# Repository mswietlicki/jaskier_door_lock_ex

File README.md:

# 12 V Linear-Actuator Door Lock

ESPHome door lock for Home Assistant: an ESP32 drives a **DRV8871** H-bridge into a
12 V linear actuator, with an **INA219** high-side shunt reading motor current.
End of travel *and* obstructions are both detected from that current — no extra sensors.
Powered from a 4S LiFePO₄ pack via an **MH-MINI-360** buck.

Three variants share the same per-door state machine:

| Variant | Config | ESP | Doors |
|---|---|---|---|
| **A** | `door_lock_a.yaml` | ESP32-C3-Zero (Waveshare) | 1 |
| **B** | `door_lock_b.yaml` | ESP32-S3-DevKitC-1 | 4, fully independent, one board |
| **C** | `door_lock_c.yaml` + [`hardware/door-lock-c/`](hardware/door-lock-c/README.md) | ESP32-C3 SuperMini, socketed | 2, on a hand-assembled JLCPCB board with door contacts and optional RS485 (Modbus RTU) |

Everything below describes variant A; [Variant B](#variant-b--four-doors-one-board)
documents only what differs (pins, addresses, BOM, power). Variant C is documented with its
board in [`hardware/door-lock-c/README.md`](hardware/door-lock-c/README.md).

| | |
|---|---|
| Pack | 4S LiFePO₄ · 12.8 V nominal · 10.0 – 14.6 V |
| Measured stall current | ≈ 0.50 A |
| Default thresholds | 0.40 A stall / 0.60 A hard limit / 0.01 A idle |
| Shunt | 0.1 Ω · 0.8 mA resolution |
| I²C | GPIO8 (SDA) / GPIO9 (SCL) · address 0x40 |
| Bridge | GPIO6 (IN1) / GPIO7 (IN2) · full on/off, **no PWM** |

## Repository layout

```
hardware/door-lock-c/        variant C - two-door PCB (KiCad 10, JLCPCB files, generator scripts)
door_lock_a.yaml             variant A - single door on an ESP32-C3-Zero
door_lock_b.yaml             variant B - four doors on an ESP32-S3-DevKitC-1
door_lock_c.yaml             variant C - two doors, door contacts, Modbus RTU on RS485
packages/door.yaml           one door's state machine (variants B and C)
packages/door_switches.yaml  one door's position switches + button (variant B)
packages/door_contact.yaml   one door's wired magnetic contact (variant C)
secrets.yaml.example         copy to secrets.yaml and fill in
docs/wiring.html             full illustrated build document for variant A
docs/wiring_b.html           full illustrated build document for variant B
docs/diagrams/
  fig1-wiring.svg            complete wiring diagram, all pinouts (variant A)
  fig2-position-switches.svg optional position feedback
  fig3-move-outcomes.svg     how a move terminates
  figB1-wiring.svg           complete wiring diagram, four doors (variant B)
```

---

## Read this first

> [!CAUTION]
> **Set the buck converter output before connecting anything to it.**
> The MH-MINI-360 ships with its trimpot in an arbitrary position and will happily pass
> close to 12 V straight through. The ESP32-C3-Zero's `5V` pad accepts **3.7 – 6 V**;
> above that you destroy the regulator and probably the chip.
> Wire U4 to the pack *with nothing on its output*, measure OUT+ to OUT−, trim to
> **5.00 V**, power down, then connect U1.

> [!WARNING]
> **Two things a door lock has to get right.** Keep a mechanical override — a key
> cylinder or thumb turn — that works with the electronics dead. And make sure the
> actuator cannot trap anyone inside: the bolt must be releasable from the protected
> side without power.

The firmware drives the bridge **fully on, never PWM**. PWM would chop the current the
INA219 sees and make stall detection unreliable, so the actuator only ever runs at full
speed. Adding soft-start later means an RC filter on the sense path and higher thresholds.

---

## Wiring

**The current path is the whole design.** Pack → F1 → +12 V rail → U3's 0.1 Ω shunt →
U2 Power + → motor. Because the shunt sits upstream of the bridge, one INA219 gives you
both motor current *and* pack voltage, and its bus-voltage input never sees the chopped
motor node. U3's own GND runs back to the star point as a separate wire so motor return
current does not corrupt the measurement.

U2's `VM` and `GND` header pins are the same nets as the `Power ±` screw terminal —
populate one or the other, not both.

### Net list

Build in this order. Everything in the 12 V group carries motor current: keep it short,
thick, and away from the I²C pair.

| Net | From | To | Wire | Notes |
|---|---|---|---|---|
| `+12V_BAT` | BAT1 + | F1 | 18 AWG | Screw terminal at the board edge |
| `+12V_BAT` | F1 | D1 anode | 18 AWG | D1 optional; omit and polarity is on you |
| `+12V` | D1 cathode | +12 V rail | 18 AWG | Rail = a length of bare 18 AWG along the board |
| `+12V` | +12 V rail | U4 IN+ | 22 AWG | Logic supply branch |
| `+12V` | +12 V rail | U3 VIN+ | 20 AWG | Motor branch enters the shunt here |
| `VM` | U3 VIN− | U2 Power + | 20 AWG | Shunt output — the only path to the bridge |
| `M+` | U2 Motor + | M1 lead A | 20 AWG | Twist the pair; swap A/B if travel is inverted |
| `M−` | U2 Motor − | M1 lead B | 20 AWG | C3 100 nF across the two, at the motor end |
| `+5V` | U4 OUT+ | U1 5V | 24 AWG | **Verify 5.00 V before connecting** |
| `+3V3` | U1 3V3 | U3 VCC | 26 AWG | Also supplies the module's I²C pull-ups |
| `SDA` | U1 GPIO8 | U3 SDA | 26 AWG | Keep under 15 cm, away from motor leads |
| `SCL` | U1 GPIO9 | U3 SCL | 26 AWG | Same pin as the BOOT button — see pinout note |
| `IN1` | U1 GPIO6 | U2 IN1 | 26 AWG | High = drive towards UNLOCKED |
| `IN2` | U1 GPIO7 | U2 IN2 | 26 AWG | High = drive towards LOCKED |
| `IN1` | U2 IN1 | R1 10 k → GND | — | Fit at U2's header, not at U1 |
| `IN2` | U2 IN2 | R2 10 k → GND | — | Holds the bridge off while U1 resets |
| `C1` | U2 Power + | U2 Power − | — | 100 µF / 25 V electrolytic, under 20 mm of lead |
| `C2` | U2 Power + | U2 Power − | — | 100 nF ceramic, right next to C1 |
| `GND` | BAT1 − | GND rail | 18 AWG | This point is the star — nothing daisy-chains past it |
| `GND` | U2 Power − | GND rail | 20 AWG | Motor return; own wire straight to the star |
| `GND` | U4 IN− and OUT− | GND rail | 22 AWG | Both pads, joined at the board |
| `GND` | U1 GND | GND rail | 24 AWG | Own wire — do not share with the motor return |
| `GND` | U3 GND | GND rail | 24 AWG | Own wire — this is the measurement reference |

### Perfboard layout

The schematic is drawn as three horizontal rails because that is how it should be built:
a bare 18 AWG +12 V rail along the top, a bare 18 AWG GND rail along the bottom, logic
between them.

- **C1 and C2 go at U2's power terminals**, not near the battery. Perfboard wire has real
  inductance, and a 12 V motor switching on at the far end of 30 cm of it will brown out
  the bridge without them.
- **Keep the motor loop tight.** U3 → U2 → motor terminals should be the shortest run on
  the board. Twist the two motor leads together for their whole length.
- **Star the grounds.** Four separate returns land at BAT1 −: U2's motor return, U4's,
  U1's, U3's. Do not let U1 or U3 ground *through* U2's return path — that is the single
  most common cause of nonsense current readings.
- **Put the I²C pair on the opposite side of U1** from the motor wiring, under ~15 cm.
  The 10 k pull-ups on the INA219 module are weak; if the bus scan is flaky, add 4.7 k
  from SDA and SCL to 3V3.
- **Screw terminals for anything leaving the board** — pack, motor. Soldered flying leads
  on perfboard fail at the joint under vibration, and a door slams a lot.
- **Fuse before everything.** F1 is the only thing between a 4S LiFePO₄ pack and a shorted
  perfboard trace; that pack will deliver tens of amps into a fault without noticing.

---

## Pinouts

### U1 — ESP32-C3-Zero (Waveshare)

18 castellated pads at 2.54 mm: three power, fifteen GPIO. GPIO11–GPIO17 are consumed by
the stacked 4 MB flash and are not brought out.

> Pin positions assume the board mounted with **USB-C uppermost** and the power pads on
> the left edge. Verify against the silkscreen before soldering.

| Edge | Pad | Wired to | Constraints worth knowing |
|---|---|---|---|
| L1 | `5V` | U4 OUT+ | Accepts 3.7 – 6 V. Feeds the on-board regulator. |
| L2 | `GND` | GND rail | — |
| L3 | `3V3` | U3 VCC | Regulator output. Budget ~200 mA for peripherals. |
| L4 | `GPIO0` | SW1 (optional) | ADC1_CH0. Also the 32 kHz XTAL pin — fine as digital I/O. |
| L5 | `GPIO1` | SW2 (optional) | ADC1_CH1. |
| L6 | `GPIO2` | *free* | **Strapping pin** — must be high or floating at boot. Do not pull it down. |
| L7 | `GPIO3` | *free* | ADC1_CH3. |
| L8 | `GPIO4` | *free* | ADC1_CH4. |
| L9 | `GPIO5` | SW3 button (optional) | ADC2 — unusable as an ADC while Wi-Fi is on. Digital is fine. |
| R1 | `GPIO6` | U2 IN1 | Plain GPIO, no strapping role. Good choice for the bridge. |
| R2 | `GPIO7` | U2 IN2 | Plain GPIO. |
| R3 | `GPIO8` | U3 SDA | Strapping pin that must be *high* at boot — the I²C pull-up satisfies that. |
| R4 | `GPIO9` | U3 SCL | BOOT button. Held low at reset it enters the ROM bootloader; I²C idles high so it never does. Don't press BOOT while the bus is live. |
| R5 | `GPIO10` | on-board WS2812 | Health and action indicator, RGB data order; no external wiring. |
| R6 | `GPIO18` | *reserved* | USB D−. Leave open or you lose USB flashing and logging. |
| R7 | `GPIO19` | *reserved* | USB D+. |
| R8 | `GPIO20` | *free* | UART0 RX. Free here because logging goes over USB. |
| R9 | `GPIO21` | *free* | UART0 TX. |

### ESP32-C3-Zero on-board LED

The firmware uses the GPIO10 WS2812 as a self-contained health and action indicator:

| LED | Meaning |
|---|---|
| Amber slow pulse | Firmware is alive and joining Wi-Fi. |
| Blue slow pulse | Wi-Fi is connected; waiting for the Home Assistant API. |
| Dim green | Home Assistant is connected and the lock reports locked. |
| Dim blue | Home Assistant is connected and the lock reports unlocked. |
| Dim amber | Home Assistant is connected and the position is unknown or stopped. |
| Magenta fast pulse | Locking. |
| Cyan fast pulse | Unlocking. |
| Green flash | Movement completed successfully. |
| Red fast pulse | Latched jam, timeout, current-sensor, or watchdog fault. |

The LED is driven by the application firmware, so a dark LED does not by itself prove that the board has no power. For USB recovery, hold **BOOT**, tap **RESET**, release **BOOT**, and flash the firmware while the board is in ROM download mode. See the [Waveshare ESP32-C3-Zero documentation](https://docs.waveshare.com/ESP32-C3-Zero).

### U2 — DRV8871 breakout (Adafruit 3190)

| Terminal | Type | Wired to | Notes |
|---|---|---|---|
| `Power +` | screw | U3 VIN− | 6.5 – 45 V. Same net as the header's `VM` pin. |
| `Power −` | screw | GND rail | Same net as the header's `GND` pin. |
| `Motor +` | screw | M1 lead A | OUT1 |
| `Motor −` | screw | M1 lead B | OUT2 |
| `VM` | header | *unused* | Duplicate of `Power +`. Use one or the other. |
| `IN1` | header | U1 GPIO6 | 1.5 V logic threshold — 3.3 V drive is fine. 10 k to GND. |
| `IN2` | header | U1 GPIO7 | 10 k to GND. |
| `GND` | header | *unused* | Duplicate of `Power −`. |
| R<sub>ILIM</sub> | on-board SMD | — | Sets the chip's own trip level to roughly 2 A. Leave it: F1 plus the firmware limit do the real work at 0.5 A. |

Input truth table: `00` coast (and low-power sleep) · `10` unlock · `01` lock · `11` brake.
The firmware never uses brake.

### U3 — INA219 module, 0.1 Ω shunt

| Pin | Wired to | Notes |
|---|---|---|
| `VCC` | U1 3V3 | 3.0 – 5.5 V. At 3.3 V the module's pull-ups match the ESP32's logic — no level shifter. |
| `GND` | GND rail (own wire) | Measurement reference. Route to the star point, not through the motor return. |
| `SCL` | U1 GPIO9 | 10 k pull-up on the module. |
| `SDA` | U1 GPIO8 | 10 k pull-up on the module. |
| `VIN+` | +12 V rail | High side of the shunt. Common mode up to 26 V — 12.8 V is comfortable. **Use the big pad, not the header pin.** |
| `VIN−` | U2 Power + | Low side of the shunt, and the bus-voltage sense node. **Big pad.** |
| `VIN+` / `VIN−` *(header)* | *leave empty* | Duplicates of the pads above — same copper, one 0.1 Ω shunt between them. Populate one pair only. |
| `A0` / `A1` | *open* | Both open = address 0x40. |

> [!WARNING]
> **Never bridge the shunt.** U3 brings `VIN+` and `VIN−` out twice: as large pads for
> load current, and again on the 6-way header. Each pair is the same copper. Wire the
> **big pair only** and leave the header pins empty.
>
> Land two wires from the same side of the circuit on both footprints and you short across
> the shunt. The motor still runs normally, so nothing looks broken — but current reads
> ≈ 0 A forever, every move ends instantly as "current collapsed", and jam detection never
> fires. Before wiring, check with a meter: `VIN+` to `VIN−` should read about **0.1 Ω**,
> and big-to-small on the same name about **0 Ω**.

### U4 — MH-MINI-360 (MP1584EN)

| Pad | Wired to | Notes |
|---|---|---|
| `IN+` | +12 V rail | 4.75 – 23 V. A 4S LiFePO₄ pack at 14.6 V is well inside range. |
| `IN−` | GND rail | — |
| `OUT+` | U1 5V | **Set to 5.00 V with the trimpot before connecting U1.** |
| `OUT−` | GND rail | — |
| trimpot | — | Multi-turn; clockwise usually raises output. Measure, don't guess. |

---

## Optional position feedback

The firmware works without these — lock state survives a reboot in flash. But
flash-restored state is a *belief*, not a measurement: if someone moves the bolt by hand
while the board is off, it will be wrong. Two reed or micro switches turn that belief into
a fact.

Internal pull-ups are enabled in firmware, so a closed switch pulls the pin to GND and
reads as active. Leaving these pads empty is harmless — the pins float high and read
inactive. For leads longer than about 30 cm add a 100 nF cap from each pin to GND at the
ESP32 end.

**Fit them, then enable them.** Turn on the *Use position switches* entity only once SW1
and SW2 are actually installed. With it on, a closed switch ends the move immediately and
overrides the current-based verdict.

---

## How a move ends

Every move is a race between four outcomes. The firmware samples the INA219 at 20 Hz,
ignores the first 400 ms of inrush, then needs **three consecutive samples** past a
threshold before it commits — one noisy reading never triggers anything.

1. **Current collapses below `idle current`** → the actuator's internal limit switch cut
   the motor at end of stroke → `LOCKED` / `UNLOCKED`.
2. **Current rises past `stall current` after `min travel time`** → the bolt reached its
   mechanical stop → `LOCKED` / `UNLOCKED`. (This is the path for actuators without
   internal limit switches.)
3. **Current rises past `stall current` before `min travel time`** → obstruction. Coast,
   wait, drive back out for as long as it drove in (capped at 4 s) → `JAMMED` + alert.
4. **Neither threshold reached by `max travel time`** → slipping clutch, broken linkage,
   bad wiring → `JAMMED` + alert.

A fifth path isn't drawn: after inrush blanking, current above `hard current limit`
aborts on the very first sample, with no debounce. Three consecutive invalid INA219
samples abort without back-off and latch a current-sensor fault; an invalid reading is
never treated as an open actuator limit switch.

**The only thing separating ② from ③ is the clock.** A stall after `min travel time` is
the bolt arriving; the same stall before it is an obstruction. That is why `min travel
time` must be set from a measured stroke rather than guessed.

---

## Bill of materials

| Ref | Part | Spec | Notes |
|---|---|---|---|
| U1 | Waveshare ESP32-C3-Zero | ESP32-C3FH4, 4 MB | Header version (`-M`) saves soldering castellations |
| U2 | Adafruit DRV8871 breakout | 6.5 – 45 V, 2 A / 3.6 A pk | — |
| U3 | INA219 module | 0.1 Ω, 0x40, ±3.2 A | Keep the 0.1 Ω shunt — at 0.5 A you want the resolution |
| U4 | MH-MINI-360 | MP1584EN, 1.8 A | Buy two; the trimpots are fragile |
| M1 | 12 V linear actuator | stall ≈ 0.5 A measured | Note whether it has internal limit switches |
| BAT1 | LiFePO₄ 4S pack | 12.8 V nom, BMS | 10.0 – 14.6 V across the whole cycle |
| F1 | Fuse + holder | 2 A slow-blow | Or a 1.5 A polyfuse if you prefer self-resetting |
| D1 | Schottky diode | SS54 / 1N5822 | Optional reverse-polarity protection, ~0.4 V drop |
| C1 | Electrolytic | 100 µF / 25 V | 35 V if the pack ever sees a charger |
| C2, C3 | Ceramic | 100 nF / 50 V | C2 at U2, C3 across the motor |
| R1, R2 | Resistor | 10 kΩ ¼ W | IN1 / IN2 pull-downs |
| SW1, SW2 | Reed or micro switch | NO, dry contact | Optional position feedback |
| SW3 | Momentary push-button | NO | Optional local override |

---

## Flashing

```bash
cp secrets.yaml.example secrets.yaml
```

Fill in `secrets.yaml`, generating the API key with:

```bash
openssl rand -base64 32
```

Then, with U1 on USB-C (use `door_lock_b.yaml` for variant B):

```bash
esphome run door_lock_a.yaml
```

Subsequent updates go over the air. Logs are available with:

```bash
esphome logs door_lock_a.yaml
```

## Commissioning

In this order. Steps 1–4 happen with the motor disconnected.

1. **Set the buck.** U4 on the pack, nothing on its output, meter on OUT+/OUT−, trim to
   5.00 V. Power down.
2. **Bring up U1 alone.** Flash over USB-C, then power it from U4 and confirm it joins
   Wi-Fi and Home Assistant.
3. **Confirm I²C.** The log should print `Found i2c device at address 0x40` at boot. If it
   doesn't, add 4.7 k pull-ups before doing anything else.
4. **Check the sense path.** With the motor unplugged but the 12 V branch live, *supply
   voltage* should read the pack voltage and *motor current* a few milliamps. If current
   reads a dead flat 0.000 A, suspect a bridged shunt before anything else — measure 0.1 Ω
   across U3's `VIN+`/`VIN−` with the power off.
5. **Verify direction.** Connect the motor. Press *Jog unlock* — a fixed 400 ms nudge with
   no protection logic. If the bolt goes the wrong way, swap the two motor leads at U2.
6. **Measure the real currents.** Watch *motor current* while jogging repeatedly and note
   the free-running value. Then hold the bolt and jog again to confirm the ~0.5 A stall.
7. **Set the thresholds** from what you measured (table below).
8. **Measure the stroke.** One full move; read *last move duration*. Set `min travel time`
   to about 70 % of it and `max travel time` to about 150 %.
9. **Test the jam path.** Block the bolt with something soft mid-travel and command a move.
   It must stop, reverse out, report *Jammed*, and set the fault sensor.

### Setting the thresholds

All six are Home Assistant `number` entities stored in flash — no reflashing to tune. What
matters is that the free-running current sits clearly between `idle current` and
`stall current`.

| Entity | Default | How to pick it |
|---|---|---|
| Idle current | 0.01 A | Well below the commissioned 0.04–0.06 A free-running current, above the ≈0.003 A standing reading. Three samples under this = limit switch opened. |
| Stall current | 0.40 A | Roughly midway between free-running and the 0.5 A stall. Raise it if normal moves trip a false jam. |
| Hard current limit | 0.60 A | Just above stall. After inrush blanking it trips on a single sample, with no debounce. |
| Inrush blanking | 400 ms | Long enough to cover the startup spike. Shorten only if the logs show the spike is over sooner. |
| Min travel time | 1500 ms | ≈ 70 % of the measured full stroke. Below this, a stall means an obstruction. |
| Max travel time | 4500 ms | Commissioned 1.7–2.8 s stroke plus cold-weather margin. Reaching it is a timeout fault. |

> [!IMPORTANT]
> **If free-running current is close to stall current.** A 0.5 A stall is low, which means
> the gap between running and stalled may be narrow — and that gap is what the whole
> detection scheme rests on. If you measure, say, 0.35 A running against 0.50 A stalled,
> current alone is too coarse: fit SW1/SW2 and let the switches call end-of-travel, leaving
> current detection purely as the jam guard.

---

## Home Assistant entities

| Entity | Type | What it's for |
|---|---|---|
| Door lock | `lock` | Lock / unlock. Reports Locking, Unlocking, Locked, Unlocked, or **Jammed**. |
| Motor current | `sensor` | 1 Hz. The state machine runs off a faster internal copy at 20 Hz. |
| Supply voltage | `sensor` | Pack voltage from the same INA219 — free LiFePO₄ monitoring. |
| Last move peak current | `sensor` | Diagnostic. Trend it and you'll see the mechanism stiffening before it fails. |
| Last move duration | `sensor` | Diagnostic. Also how you set the travel-time thresholds. |
| Fault | `binary_sensor` | Problem class. Latches until cleared. |
| Last result | `text_sensor` | Plain text: `locked`, `obstruction - stalled mid-travel`, and so on. |
| Stop | `button` | Aborts a move immediately, state goes unknown. |
| Clear fault | `button` | Drops the fault flag; the LED returns to the current connectivity and lock state. |
| Jog unlock / Jog lock | `button` | 400 ms bench nudge, no protection logic. Disabled by default; enable only while commissioning. |
| Use position switches | `switch` | Off by default. Turn on once SW1/SW2 exist. |
| Six thresholds | `number` | Config category. Stored in flash. |

### Alerting on a failed move

Two independent hooks — pick whichever fits. The lock entity going to `jammed`:

```yaml
automation:
  - alias: Door lock jammed
    trigger:
      - platform: state
        entity_id: lock.door_lock
        to: "jammed"
    action:
      - service: notify.mobile_app_phone
        data:
          title: Door lock failed
          message: >-
            {{ states('sensor.door_lock_last_result') }} —
            peak {{ states('sensor.door_lock_last_move_peak_current') }} A
```

…or the event the firmware fires, which carries the detail as attributes:

```yaml
automation:
  - alias: Door lock fault event
    trigger:
      - platform: event
        event_type: esphome.door_lock_fault
    action:
      - service: notify.mobile_app_phone
        data:
          title: "Door lock: {{ trigger.event.data.reason }}"
          message: >-
            While {{ trigger.event.data.direction }} —
            {{ trigger.event.data.peak_current }} A after
            {{ trigger.event.data.travel_ms }} ms
```

---

## Variant B — four doors, one board

`door_lock_b.yaml` runs **four fully independent doors** from one ESP and one perfboard.
Each door is a verbatim copy of the variant A state machine (factored out into
`packages/door.yaml` and included four times, with its position switches and button in
`packages/door_switches.yaml`), so everything above — move outcomes,
thresholds, jam handling, commissioning — applies per door. Doors never wait on each
other; any or all four can move at once. A "close all" in Home Assistant is simply a
script/automation that calls `lock.lock` on all four entities.

The full illustrated build document for this variant — wiring diagram, net list,
complete DevKitC-1 pinout, BOM, commissioning — is **[docs/wiring_b.html](docs/wiring_b.html)**
(open in a browser).

### What changes against variant A

| | Variant A | Variant B |
|---|---|---|
| ESP | ESP32-C3-Zero | **ESP32-S3-DevKitC-1** — the C3 has ~11 usable GPIOs, four doors need ~23 |
| H-bridge | 1 × DRV8871 | 4 × DRV8871, one per door |
| Current sense | 1 × INA219 @ 0x40 | 4 × INA219 on the **same I²C bus** @ 0x40 / 0x41 / 0x44 / 0x45 |
| Pull-downs | R1, R2 | 10 k on **all eight** IN pins (R1–R8) |
| Fuse F1 | 2 A slow-blow | **5 A slow-blow** — four actuators stalling together draw ~2 A plus inrush |
| Supply voltage entity | from the INA219 | from door 1's INA219 only (all four sit on the same rail) |
| Status LED | per-move | aggregate: red = any fault · white = any door moving · green flash = a move finished |

Each door keeps its own 12 V branch: rail → its INA219 shunt → its DRV8871 → its motor,
exactly as in Figure 1, replicated four times off the shared +12 V and GND rails. All the
variant A layout rules still hold — star grounds (each INA219 and each bridge return runs
its own wire to the star), tight motor loops, C1/C2 at *every* bridge's power terminals,
I²C away from motor wiring.

### INA219 addressing

Solder jumpers on each module set the address:

| Door | A1 | A0 | Address |
|---|---|---|---|
| 1 | open | open | 0x40 |
| 2 | open | bridged | 0x41 |
| 3 | bridged | open | 0x44 |
| 4 | bridged | bridged | 0x45 |

Confirm with the boot log: the I²C scan must find all four addresses. Four modules also
mean four sets of 10 k bus pull-ups in parallel (≈ 2.5 k effective) — that is fine at
400 kHz; do not add the extra 4.7 k resistors from the variant A notes.

### Pin map (ESP32-S3-DevKitC-1)

| Door | IN1 (unlock) | IN2 (lock) | SW locked | SW unlocked | Button | INA219 |
|---|---|---|---|---|---|---|
| 1 | GPIO4 | GPIO5 | GPIO10 | GPIO11 | GPIO39 | 0x40 |
| 2 | GPIO6 | GPIO7 | GPIO12 | GPIO13 | GPIO40 | 0x41 |
| 3 | GPIO15 | GPIO16 | GPIO14 | GPIO21 | GPIO41 | 0x44 |
| 4 | GPIO17 | GPIO18 | GPIO1 | GPIO2 | GPIO42 | 0x45 |

Shared: **GPIO8** SDA · **GPIO9** SCL · **GPIO48** on-board WS2812 (older DevKitC-1
revisions route the LED to GPIO38 — change `pin_rgb` if yours does).

Avoided on purpose: GPIO0 / 3 / 45 / 46 (strapping), GPIO19 / 20 (USB),
GPIO43 / 44 (UART0), GPIO35 – 37 (used by octal-PSRAM boards). Position switches and
buttons are optional exactly as in variant A — unfitted pins float high on the internal
pull-up and read inactive.

### BOM delta

Quantities against the variant A BOM: U2 ×4, U3 ×4 (with address jumpers set), M1 ×4,
R1–R8 (eight 10 k pull-downs), C1/C2 ×4 (at each bridge), C3 ×4 (at each motor),
F1 becomes 5 A. U1 becomes an ESP32-S3-DevKitC-1 (any flash size; N8R2 is plenty).
One MH-MINI-360 still powers everything — the ESP plus four INA219s draw well under
its 1.8 A.

### Commissioning

Run the variant A commissioning sequence **once per door** — each door has its own six
threshold entities, jog buttons, and *use position switches* toggle, all prefixed
"Door 1…4" in Home Assistant. Doors with different actuators, strokes, or friction get
different thresholds; that is the point of keeping the config per door.

The fault event carries a `door` field, so one automation covers all four:

```yaml
automation:
  - alias: Any door lock fault
    trigger:
      - platform: event
        event_type: esphome.door_lock_fault
    action:
      - service: notify.mobile_app_phone
        data:
          title: "{{ trigger.event.data.door }}: {{ trigger.event.data.reason }}"
          message: >-
            While {{ trigger.event.data.direction }} —
            {{ trigger.event.data.peak_current }} A after
            {{ trigger.event.data.travel_ms }} ms
```

And "close all" is one service call:

```yaml
script:
  close_all_doors:
    sequence:
      - service: lock.lock
        target:
          entity_id:
            - lock.door_locks_door_1
            - lock.door_locks_door_2
            - lock.door_locks_door_3
            - lock.door_locks_door_4
```

---

## Firmware notes

Decisions in `door_lock_a.yaml` / `packages/door.yaml` that are easy to undo by accident:

- **No PWM on the bridge.** `output: gpio`, not `ledc`. Switching to PWM chops the current
  the shunt sees and breaks every threshold above.
- **Both inputs low means coast**, and the DRV8871 drops into low-power sleep after about a
  millisecond of it — what you want between moves on a battery. The brake state (both
  inputs high) is never used.
- **The fast current sensor is `internal: true`** and polled at 50 ms. Everything Home
  Assistant sees is a slower derived copy, so the API isn't flooded with 20 values a second.
- **A 500 ms watchdog interval** force-coasts the bridge if it is ever still energised well
  past `max travel time`, independently of the move script. Combined with R1/R2 holding the
  inputs down through reset, there is no state in which the actuator runs unattended.
- **Reversing after a jam is time-based** — it drives back out for as long as it drove in,
  capped at 4 s. That path has no stall detection of its own, deliberately: if the
  obstruction is on the retreat side too, you want the fault raised rather than an infinite
  shuffle.

---

## References

- [Waveshare ESP32-C3-Zero documentation](https://docs.waveshare.com/ESP32-C3-Zero)
- [ESP32-C3-Zero pinout reference](https://www.espboards.dev/esp32/esp32-c3-zero/)
- [DRV8871 breakout — Botland](https://botland.com.pl/sterowniki-silnikow-dc/7043-drv8871-jednokanalowy-sterownik-silnikow-45v36a-adafruit-3190-5904422335373.html)
- [INA219 module — Gotronik](https://www.gotronik.pl/ina219-dwukierunkowy-czujnik-pradu-z-szyna-i2c-p-5736.html)

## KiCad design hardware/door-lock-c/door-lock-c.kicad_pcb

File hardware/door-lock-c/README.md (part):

# Door lock C: two doors, ESP32-C3 SuperMini, optional RS485

A board for two 12 V linear-actuator door locks. Each door gets what variant A uses as
breakout boards (a DRV8871 H-bridge and an INA219 on a 0.1 Ω high-side shunt), plus an input
for a wired magnetic door contact. One socketed ESP32-C3 SuperMini runs both doors. An optional
RS485 port lets Home Assistant lock and unlock over Modbus RTU through the van's RS485 gateways
when Wi-Fi is down. It is a bare JLCPCB board with parts from LCSC, assembled by hand, and is
ordered together with the CAN-B node (jaskier repo, `hardware/canb-node`).

**Status: designed 5 November 2026, boards and parts ordered 5–6 November 2026 (see
[Ordering](#ordering)), not built, not tested.** Firmware:
[`door_lock_c.yaml`](../../door_lock_c.yaml), see [Firmware](#firmware). KiCad 10 project: ERC 0 violations, DRC 0
violations, 0 unconnected, schematic and board in parity.

## What it does

- **Two independent doors.** Each door has the same current path as variant A: bank → 0.1 Ω shunt
  → DRV8871 VM → actuator. The INA219 on that shunt reads the motor current at 20 Hz and the
  bank voltage. Door A's INA219 is at I²C address 0x40, door B's at 0x44.
- **A door contact input per door.** A wired magnetic contact (reed, NO or NC) goes between DOOR
  and GND on the door's terminal. It has a 10 kΩ pull-up and a 1 kΩ + 100 nF filter for the long
  cable. The firmware chooses the polarity. With nothing connected the input reads open.
- **Optional RS485.** An SP3485 (3.3 V) on UART0, with the driver enable held low while the
  ESP32 boots, and an SM712 clamp on A/B. J4 has two A/B/GND sets for a bus that passes through.
  The 120 Ω termination sits on a 2-pin header: fit the jumper cap on the last device of the bus.
  A 680 Ω fail-safe bias is on solder jumpers (open). Leave J4 empty and the board works on
  Wi-Fi alone.
- **Socketed SuperMini.** Two 1×8 female headers. The antenna sits at the board edge over a copper
  keep-out. The USB-C end faces the board with only low SMD parts in front of it, so a cable can
  reach it with the module in its socket.
- **Status LED.** One WS2812B-type RGB LED (XL-5050RGBC-2812B, 5050, side pads) on IO2. It is
  powered from 5 V through a diode (about 4.3 V), so the 3.3 V data line meets its input threshold.
- **Supply:** from the 4S LiFePO₄ house bank, through a 1.1 A PTC, a P-MOSFET reverse-polarity
  switch, a 16 V TVS and 100 µF + 10 µF. A 5 V module (K7805-500R3, the CAN-B part) feeds the
  SuperMini through a Schottky, so USB and the 12 V supply never push into each other.
- **Extension header J7:** 3.3 V, I²C (SDA/SCL), IO7, 5 V and GND, for a sensor or a button.

## What the van's readings changed

Home Assistant's recorder covered 26 October to 5 November 2026 for the back door lock (variant A,
`lock.jaskier_back_door_lock_door_lock`):

| Measurement | Value |
|---|---|
| Stroke, locking | 1.83–1.95 s |
| Stroke, unlocking | 2.01–2.07 s |
| Running current (1 Hz samples during moves) | 0.052–0.066 A |
| Peak per move (20 Hz, inrush included) | 0.07–0.18 A |
| Stall (two jams on 3 November) | 0.548 A and 0.559 A at 13.0 V |
| Standing current | 0.1–3 mA |
| Bank voltage | 12.61–14.31 V |
| Moves | 7: 2 locks and 3 unlocks that ended normally (current collapse at the actuator's end switch), plus 2 jams. One more lock (1.87 s) is from before the window |
| Jams | 3 November 13:47: two unlocks stalled at 0.53 s and 0.55 s, then the third, 6 s later, unlocked normally in 2.01 s |
| Connectivity | 17 "unavailable" gaps of 2–6 s, each at the same second as one of the front controller's: Home Assistant restarts, not Wi-Fi drops. No reboots (the last-move values survived every gap) |

What this changed on the board:

| Change | Why |
|---|---|
| DRV8871 current limit 1.14 A (R_ILIM 56 kΩ) | The Adafruit breakout's 30 kΩ sets about 2.1 A, four times the 0.55 A stall. 1.14 A is still twice the stall, so a normal move or a stall never reaches it. It limits a shorted actuator cable in the driver itself, whatever the firmware does |
| P-MOSFET instead of a series diode for reverse polarity | The INA219 measures the bank behind the protection. A Schottky would make the reading 0.2–0.45 V low, depending on the load. The FET drops about 0.05 V at full load and nothing at rest |
| 16 V TVS | The bank peaked at 14.3 V. The INA219's bus input is rated 26 V absolute maximum, and SMAJ16A clamps below that |
| 1.1 A PTC | Both actuators stalling at once draw about 1.1–1.2 A for the 0.55 s the firmware needs to stop them, which is far too short to trip it. Normal moves draw 0.15 A for both doors |
| Door contact inputs | Asked for. They also explain jams like 3 November's: a bolt bound by a door pulled against its seal. The firmware can report the door open or shut, refuse to lock an open door and lock when it closes, also over RS485 |
| RS485 | Asked for: control that does not depend on Wi-Fi |

The firmware thresholds of variant A still fit these readings. Idle 0.01 A is well below the
0.05 A running current, stall 0.40 A sits between 0.18 A and 0.55 A, min travel 1.5 s is
75–82 % of the strokes, and max travel 4.5 s is more than twice the longest. The hard limit of
0.60 A is only 8 % above the 13.0 V stall: a stall at 14.4 V may end as "hard limit" rather than
"stall". Both are jams, so it changes only the message. One firmware change worth making: after
an early stall on an unlock, retry once before latching the jam, since the third manual attempt
on 3 November worked.

## Connections

All wires enter from the board edge: power on the left, doors and RS485 at the bottom. The
terminals are 3.5 mm pitch screw terminals.

### J1, power

| Pin | Label | Connect to |
|---|---|---|
| 1 | +12V | House bank +, through a 2–3 A fuse at the bank |
| 2 | GND | House bank − |

### J2 (door A) and J3 (door B)

| Pin | Label | Connect to |
|---|---|---|
| 1 | M+ | Actuator lead A (swap with M− if the bolt moves the wrong way) |
| 2 | M− | Actuator lead B |
| 3 | DOOR | Door contact, one wire |
| 4 | GND | Door contact, other wire |

Twist the actuator pair. A powered (three-wire) door sensor needs its supply from J7.

### J4, RS485

| Pin | Label | Signal |
|---|---|---|
| 1, 4 | A | RS485 A (non-inverting) |
| 2, 5 | B | RS485 B (inverting) |
| 3, 6 | GND | Signal ground |

The two sets are joined on the board: the bus comes in on one and goes on from the other. On the
last device, use one set and terminate.

- **TERM 120R (JP1):** a 2-pin header with a 120 Ω resistor behind it across A–B. Fit the jumper
  cap when this board ends the bus, leave it off when the bus continues from J4.
- **BIAS (JP2 and JP3):** solder jumpers, 680 Ω from A to 3.3 V and from B to GND. Bridge both only
  if nothing else on the bus biases it.

### J7, extension (2.54 mm)

| Pin | Label | Signal |
|---|---|---|
| 1 | 3V3 | SuperMini 3.3 V |
| 2 | SDA | I²C (IO8), 4.7 kΩ pull-up on the board |
| 3 | SCL | I²C (IO9), 4.7 kΩ pull-up on the board |
| 4 | IO7 | Spare GPIO, no pull-up |
| 5 | 5V | 5 V behind the Schottky (about 4.6 V) |
| 6 | GND | |

Avoid I²C addresses 0x40 and 0x44 on J7: the INA219s use them.

### SuperMini socket (J5, J6)

Plug the module in component side up, antenna at the board edge ("ANT") and USB-C toward the
board ("USB-C"). The silkscreen between the socket rows repeats the module's pin labels: check they
match before plugging it in. The pin order was checked against the vendor data sheet's top-view
drawing and two independent KiCad footprints.

| Pin | Function | Notes |
|---|---|---|
| IO4 | Door A IN1 (drives towards unlocked) | 4.7 kΩ pull-down |
| IO3 | Door A IN2 (drives towards locked) | 4.7 kΩ pull-down |
| IO5 | Door B IN1 | 4.7 kΩ pull-down |
| IO6 | Door B IN2 | 4.7 kΩ pull-down |
| IO1 | Door A contact | Low = contact closed |
| IO0 | Door B contact | Low = contact closed |
| IO8 | I²C SDA | Strapping pin, held high by the pull-up. The SuperMini's blue LED is on this pin and flickers with I²C traffic |
| IO9 | I²C SCL | Strapping pin (BOOT), held high by the pull-up |
| IO2 | Status LED (WS2812B-type, 5050) | Strapping pin, 10 kΩ pull-up |
| IO10 | RS485 DE/RE | 10 kΩ pull-down: receive while the ESP32 boots |
| IO20 | RS485 RO (UART0 RX) | 10 kΩ pull-up |
| IO21 | RS485 DI (UART0 TX) | The ROM boot log on this pin never reaches the bus (DE is low) |
| IO7 | Spare, on J7 | |
| 5V | From the board's 5 V through D2 | |
| 3V3 | SuperMini regulator: INA219s, SP3485, pull-ups, J7 | |

Pins that hold their own pull-up at boot (IO2, IO8, IO9) carry nothing that a closed door contact
could pull low. A door shut at power-up cannot put the ESP32 in download mode.

## RS485 and Modbus

The board is a Modbus RTU slave (server). It is meant for one of the van's RS485 buses, or a new
one, through a Waveshare RS485-to-Ethernet gateway, and Home Assistant's Modbus integration
(`modbus/README.md` and `docs/modbus-addressing.md` in the HA config repo). It runs 9600 8N1 like
the other buses, at slave address 60 (free on every van bus on 5 November 2026). Both are
substitutions at the top of `door_lock_c.yaml`.

Register map (0-based; holding registers FC 3/4 to read, FC 6/16 to write; coils FC 1/5/15):

| Address | Kind | Content |
|---|---|---|
| coil 0 / 1 | read/write | Door A / B: 1 = locked. Write 1 to lock, 0 to unlock |
| 0 / 1 | write | Door A / B command: 1 lock, 2 unlock, 3 stop, 4 clear fault (reads 0) |
| 2 / 3 | read | Door A / B lock state: 0 unknown, 1 locked, 2 unlocked, 3 jammed, 4 locking, 5 unlocking |
| 4 / 5 | read | Door A / B contact: 0 shut, 1 open, 2 contact not in use |
| 6 / 7 | read | Door A / B fault latched: 0 / 1 |
| 8 | read | Bank voltage, mV (door A's INA219) |
| 9 / 10 | read | Door A / B last move peak current, mA |
| 11 / 12 | read | Door A / B last move duration, ms |
| 13 | read | Firmware version (100 = 1.0.0) |

A lock command (coil write 1, or command 1) while that door's contact reads open is refused
with exception 4 (device failure), and the bolt does not move. An unknown command value is
refused with exception 4 too.

Home Assistant has no Modbus lock platform. A `switch` on the coil works, for example on the
`rs485_1` hub:

```yaml
switches:
  - name: Door A lock (RS485)
    slave: 60
    address: 0
    write_type: coil
    verify:
      input_type: coil
      address: 0
sensors:
  - name: Door A lock state (RS485)
    slave: 60
    address: 2
    input_type: holding
    scan_interval: 5
```

A template lock can call `modbus.write_register` with command 1 or 2 instead.

## Firmware

[`door_lock_c.yaml`](../../door_lock_c.yaml) (repo root). It reuses the per-door packages:

| Package | Per door | What |
|---|---|---|
| `packages/door.yaml` | yes | Variant A's state machine: INA219 at 20 Hz, stall/idle/timeout, back-off, thresholds as HA numbers |
| `packages/door_contact.yaml` | yes | The door contact: "Door A door" (device class door), "use door contact" (off by default), "contact closed when shut" (on by default) |

Variant B's position switches and buttons moved out of `door.yaml` into
`packages/door_switches.yaml`, which only variant B includes. `door.yaml` now only reads three
globals that those packages write (`_at_locked`, `_at_unlocked`, `_lock_inhibit`).

- **Base:** board `esp32-c3-devkitm-1`, framework `esp-idf`, ESPHome 2026.8 or newer. The logger
  runs on `USB_SERIAL_JTAG`, so UART0 (IO20/IO21) is free for RS485.
- **Doors:** "Door A" (IO4 unlock, IO3 lock, INA219 0x40, contact IO1) and "Door B" (IO5, IO6,
  0x44, contact IO0). Every per-door entity of variant A exists once per door.
- **Door contact:** while "use door contact" is on, a lock command for an open door is refused,
  from HA and from Modbus alike, and the last result reads "refused - door open". The jog buttons
  (commissioning only, disabled by default) bypass it, as they bypass all protection.
- **No reboot without Wi-Fi or Home Assistant:** `reboot_timeout: 0s` on both `wifi` and `api`.
  The defaults reboot after 15 minutes, which would also interrupt RS485 control.
- **Status LED (IO2):**
  - red: a fault is latched
  - white: a door is moving
  - amber: no Wi-Fi
  - dim green: all quiet
  - green flash: a move finished
- **Extra entities:** supply voltage (door A's INA219), Wi-Fi signal, uptime.
- **Checked:** `esphome config` passes for variants A, B and C on ESPHome 2026.10.2, and variant C
  compiles. Not yet run on hardware.

## Design notes

- **H-bridge:** DRV8871DDAR, full on/off, never PWM (variant A's rule). Both inputs low means coast
  and sleep. The 4.7 kΩ pull-downs hold the inputs below the 0.5 V low threshold even against the
  ESP32-C3's internal pull-ups (about 45 kΩ) while it resets.
- **Current sense:** 0.1 Ω 1 % 1206 shunt per door. The INA219's IN+ and IN− run as separate
  traces from the shunt pads (Kelvin), so motor current in the supply traces does not reach the
  reading.
- **Reverse polarity:** AO3401A with its drain to the input. R1/R2 (100 kΩ each) hold Vgs at
  −Vin/2: −5 V at 10 V, −7.3 V at 14.6 V, inside the ±12 V limit. Reversed, the gate sees 0 V and
  the FET stays off.
- **Status LED supply:** 5 V − 0.7 V (1N4148W) ≈ 4.3 V. The XL-5050RGBC-2812B data sheet gives
  VDD 3.5–5.5 V and an input-high threshold of 0.7 × VDD, so about 3.0 V, and the SuperMini drives
  3.3 V. Its pins are the WS2812B's: 1 VDD, 2 DO, 3 GND, 4 DI.
- **Layout:** 80 × 64 mm, 2 layers, 1.6 mm, ground pour on both sides, stitching vias, four M3
  holes. Tracks: 1.0 mm for the input, 0.8 mm for the bank rail, 0.6 mm for motor and VM, 0.2 mm
  for signals. Clearance 0.15 mm (JLCPCB's two-layer minimum is 0.127 mm). The DRV8871 thermal
  pads have vias to the bottom pour.
- **Not on the board:** a fuse holder (fuse the supply at the bank) and position switches (the
  actuator's own end switches end every normal move, as the readings show).

## Ordering

Bare boards from JLCPCB, parts from LCSC, assembled by hand. One order covers this board, the
CAN-B node and the RS485 tee (jaskier repo, `hardware/rs485-tee`).

- **PCB:** `jlcpcb/door-lock-c-gerbers.zip`, 2 layers, 1.6 mm, 1 oz, lead-free HASL. ENIG would keep the 0.65 mm
  INA219 pads flatter, but costs €15 more. No assembly, so no edge rails and no placement file are
  needed.
- **Stencil (optional):** a top-side SMT stencil from the same zip (the F.Paste layer), worth it
  with a hot plate or hot air. Add it to the same JLCPCB cart.
- **Parts:** `jlcpcb/lcsc-order.csv` is one LCSC order for 3 door-lock-c boards, 2 CAN-B nodes and
  10 RS485 tees, with spares (+20 % or at least 2 for chip passives, +1 for the rest), including the
  TERM jumper caps. For other counts: `python tools/lcsc_order.py --door N --canb M --tee K`.
  - **Substitutions:** when LCSC runs out of a BOM part, `SUBSTITUTE` in the script buys an
    equivalent. On 5 November 2026 these were C1591 for the 100 nF (C14663, 50 left) and C1589 for
    CAN-B's 10 nF (C57112, none), both Samsung, X7R, 50 V, 0603.
  - **Loading it:** LCSC's BOM tool, "Copy & Paste", one `C-number, quantity` per line. It keeps the
    part numbers but sets every requested quantity to 1. Set the lines whose need is above LCSC's
    minimum order by hand (filter the table by part number, then re-tick Select All). LCSC rounds
    each line up to its minimum.
- **Stock on LCSC, 5 November 2026:**

  | Part | LCSC | Stock |
  |---|---|---|
  | DRV8871DDAR | C75864 | 3,497 |
  | INA219AIDCNR | C87469 | 2,324 |
  | SP3485EN | C8963 | 162,946 |
  | XL-5050RGBC-2812B | C2843785 | 1,311,820 |
  | SM712 | C172881 | 21,980 |
  | SMAJ16A | C364288 | 17,740 |
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
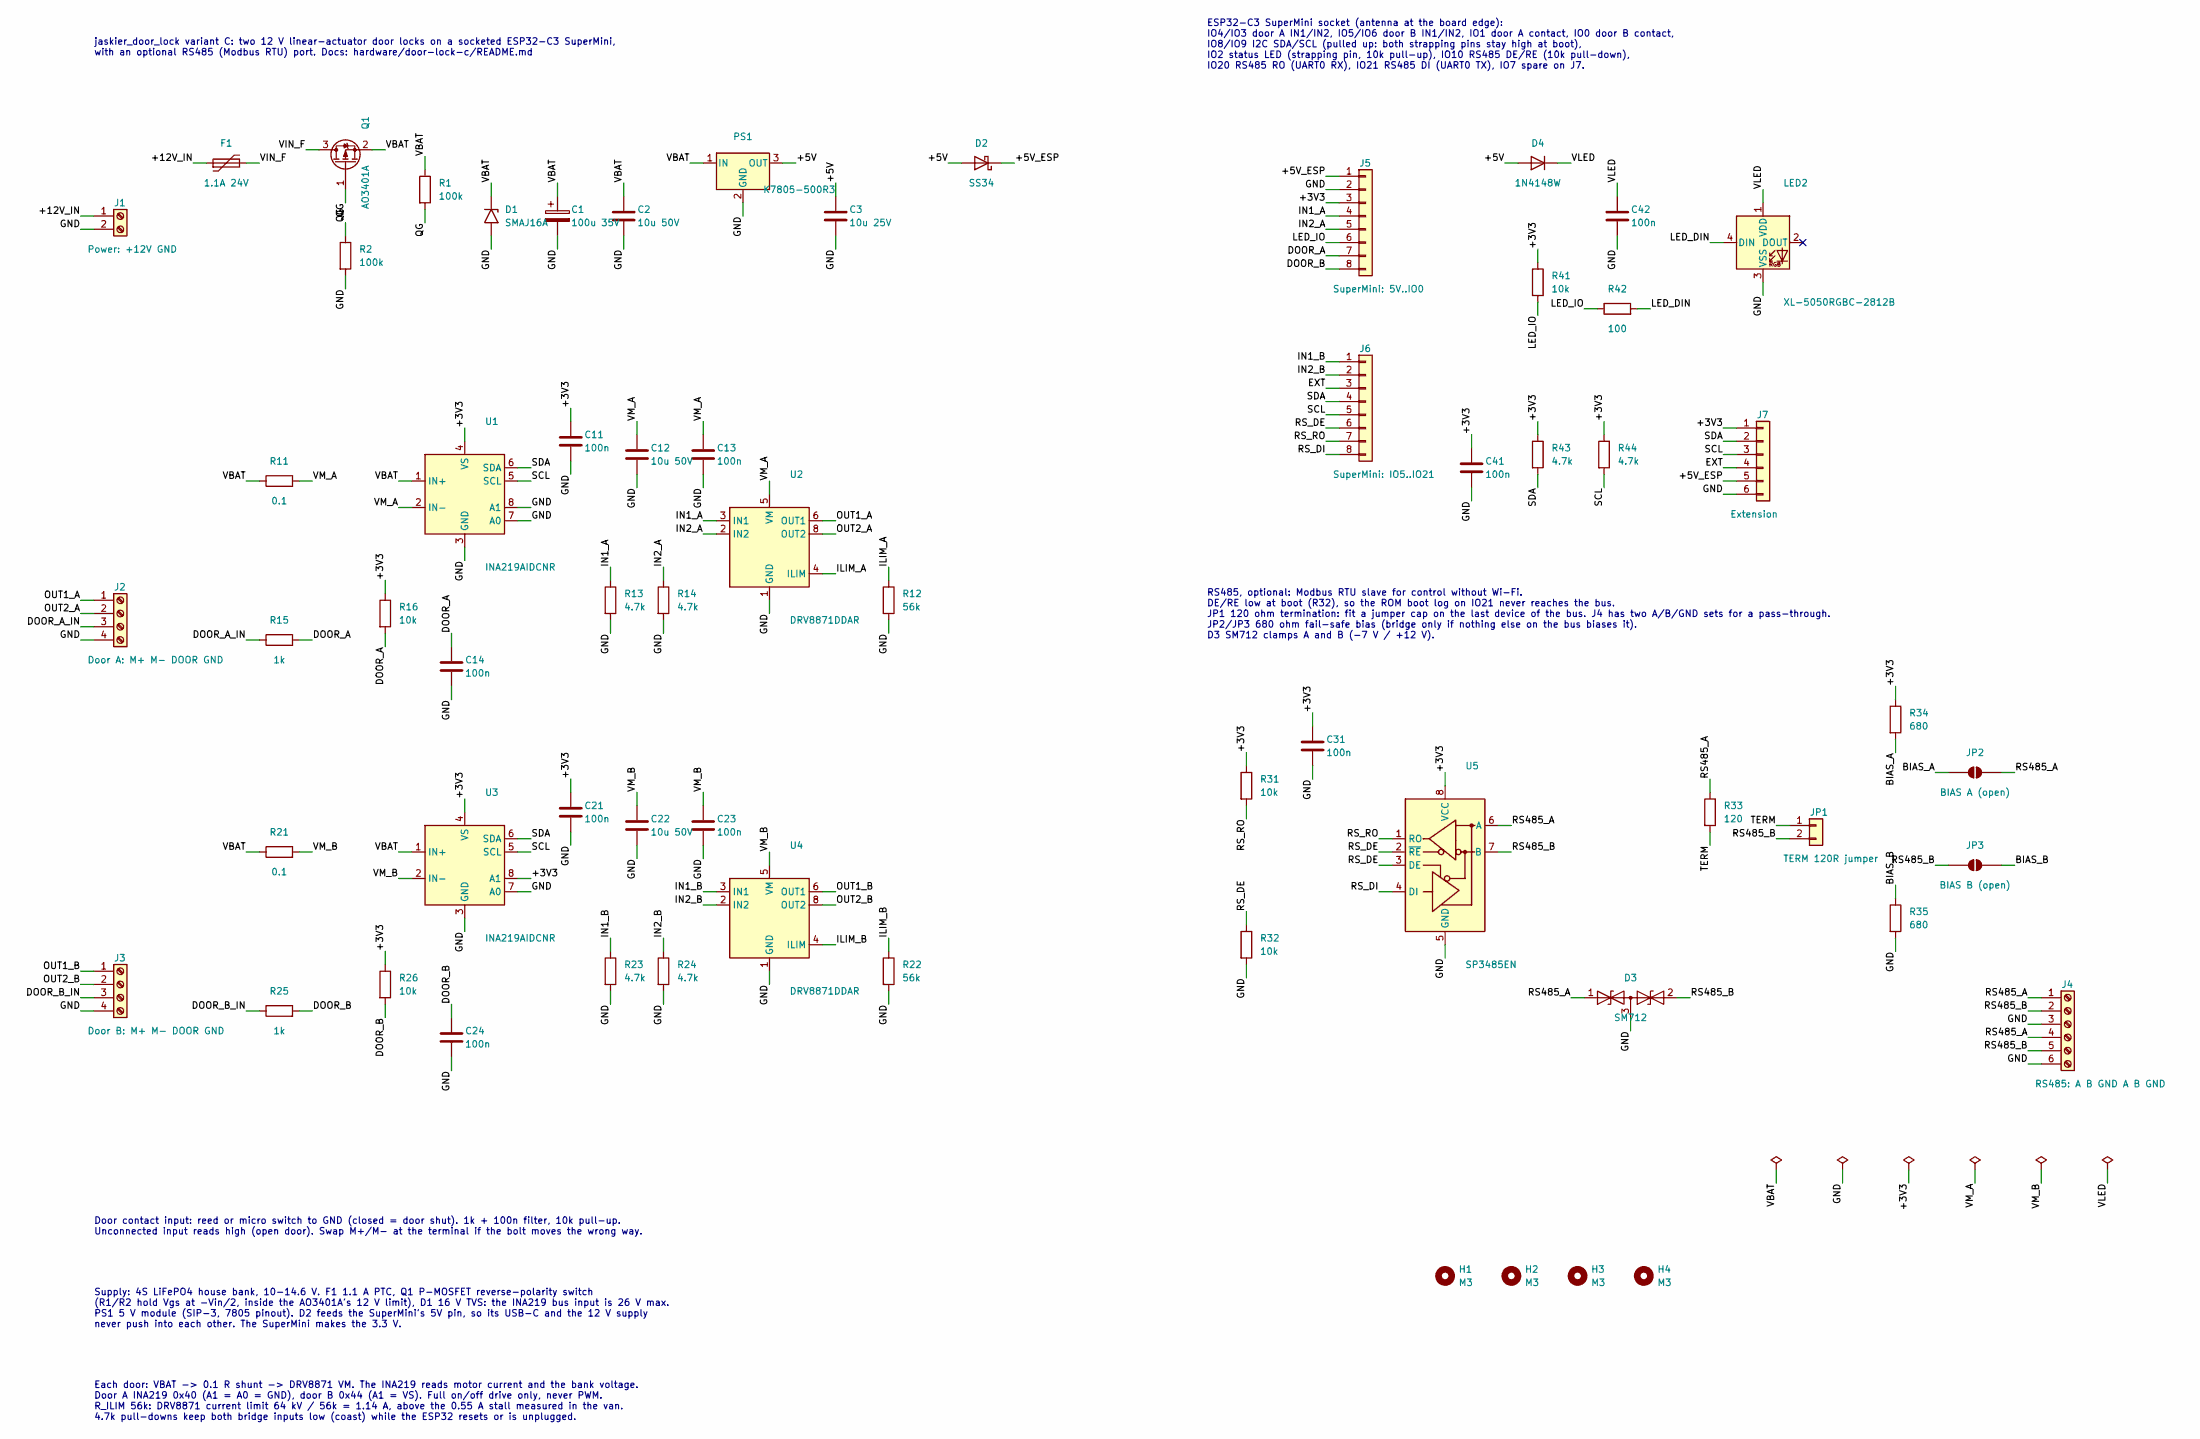
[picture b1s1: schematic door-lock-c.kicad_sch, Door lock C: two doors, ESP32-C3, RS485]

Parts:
C1: 100u 35V; CP_Elec_6.3x7.7; MPN ROQANG RVT1V101M0607; LCSC C72478
C2, C12, C22: 10u 50V; C_1206_3216Metric; LCSC C13585
C3: 10u 25V; C_0805_2012Metric; LCSC C15850
C11, C13, C14, C21, C23, C24, C31, C41, C42: 100n; C_0603_1608Metric; LCSC C14663
D1: SMAJ16A; D_SMA; LCSC C364288
D2: SS34; D_SMA; LCSC C8678
D3: SM712; SOT-23; MPN Littelfuse SM712-02HTG; LCSC C172881
D4: 1N4148W; D_SOD-123; LCSC C81598
F1: 1.1A 24V; Fuse_1812_4532Metric; MPN BHFUSE BSMD1812-110-24V (hold 1.1 A, tr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; LCSC C883149
H1, H2, H3, H4: M3; MountingHole_3.2mm_M3
J1: Power: +12V GND; TerminalBlock_Phoenix_PT-1,5-2-3.5-H_1x02_P3.50mm_Horizontal; MPN DORABO DB125-3.5-2P-GN-S; LCSC C466970
J2: Door A: M+ M- DOOR GND; TerminalBlock_Phoenix_PT-1,5-4-3.5-H_1x04_P3.50mm_Horizontal; MPN DORABO DB125-3.5-4P-GN-S; LCSC C2757925
J3: Door B: M+ M- DOOR GND; TerminalBlock_Phoenix_PT-1,5-4-3.5-H_1x04_P3.50mm_Horizontal; MPN DORABO DB125-3.5-4P-GN-S; LCSC C2757925
J4: RS485: A B GND A B GND; TerminalBlock_Phoenix_PT-1,5-6-3.5-H_1x06_P3.50mm_Horizontal; MPN DORABO DB125-3.5-6P-GN-S; LCSC C5290323
J5: SuperMini: 5V..IO0; PinSocket_1x08_P2.54mm_Vertical; MPN BOOMELE 2.54 1x8P female, 8.5 mm; LCSC C27438
J6: SuperMini: IO5..IO21; PinSocket_1x08_P2.54mm_Vertical; MPN BOOMELE 2.54 1x8P female, 8.5 mm; LCSC C27438
J7: Extension; PinHeader_1x06_P2.54mm_Vertical; MPN XFCN PZ254V-11-06P; LCSC C492405
JP1: TERM 120R jumper; PinHeader_1x02_P2.54mm_Vertical; MPN XFCN PZ254V-11-02P (cap: BOOMELE C10011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; LCSC C492401
JP2: BIAS A (open); SolderJumper-2_P1.3mm_Open_RoundedPad1.0x1.5mm
JP3: BIAS B (open); SolderJumper-2_P1.3mm_Open_RoundedPad1.0x1.5mm
LED2: XL-5050RGBC-2812B; LED_WS2812B_PLCC4_5.0x5.0mm_P3.2mm; MPN XINGLIGHT XL-5050RGBC-2812B; LCSC C2843785
PS1: K7805-500R3; Converter_DCDC_RECOM_R-78E-0.5_THT; MPN YLPTEC K7805-500R3 (6.5-36 V in, 5 V 0.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; LCSC C2992390
Q1: AO3401A; SOT-23; LCSC C15127
R1, R2: 100k; R_0603_1608Metric; LCSC C25803
R11, R21: 0.1; R_1206_3216Metric; LCSC C25334
R12, R22: 56k; R_0603_1608Metric; LCSC C23206
R13, R14, R23, R24, R43, R44: 4.7k; R_0603_1608Metric; LCSC C23162
R15, R25: 1k; R_0603_1608Metric; LCSC C21190
R16, R26, R31, R32, R41: 10k; R_0603_1608Metric; LCSC C25804
R33: 120; R_0603_1608Metric; LCSC C22787
R34, R35: 680; R_0603_1608Metric; LCSC C23228
R42: 100; R_0603_1608Metric; LCSC C22775
U1, U3: INA219AIDCNR; SOT-23-8; MPN TI INA219AIDCNR; LCSC C87469
U2, U4: DRV8871DDAR; Texas_HTSOP-8-1EP_3.9x4.9mm_P1.27mm_EP2.95x4.9mm_Mask2.4x3.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; MPN TI DRV8871DDAR; LCSC C75864
U5: SP3485EN; SOIC-8_3.9x4.9mm_P1.27mm; MPN MaxLinear SP3485EN-L/TR; LCSC C8963

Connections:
/+3V3: C11.1, C21.1, C31.1, C41.1, J5.3, J7.1, R16.1, R26.1, R31.1, R34.1, R41.1, R43.1, R44.1, U1.4 (VS), U3.4 (VS), U3.8 (A1), U5.8 (VCC)
/+5V: C3.1, D2.2 (A), D4.2 (A), PS1.3 (OUT)
/+5V_ESP: D2.1 (K), J5.1, J7.5
/+12V_IN: F1.1, J1.1
/BIAS_A: JP2.1 (A), R34.2
/BIAS_B: JP3.2 (B), R35.1
/DOOR_A: C14.1, J5.7, R15.2, R16.2
/DOOR_A_IN: J2.3, R15.1
/DOOR_B: C24.1, J5.8, R25.2, R26.2
/DOOR_B_IN: J3.3, R25.1
/EXT: J6.3, J7.4
/GND: C1.2, C2.2, C3.2, C11.2, C12.2, C13.2, C14.2, C21.2, C22.2, C23.2, C24.2, C31.2, C41.2, C42.2, D1.2 (A2), D3.3 (common), J1.2, J2.4, J3.4, J4.3, J4.6, J5.2, J7.6, LED2.3 (VSS), PS1.2 (GND), R2.2, R12.2, R13.2, R14.2, R22.2, R23.2, R24.2, R32.2, R35.2, U1.3 (GND), U1.7 (A0), U1.8 (A1), U2.1 (GND), U2.7 (GND), U2.9 (GND), U3.3 (GND), U3.7 (A0), U4.1 (GND), U4.7 (GND), U4.9 (GND), U5.5 (GND)
/ILIM_A: R12.1, U2.4 (ILIM)
/ILIM_B: R22.1, U4.4 (ILIM)
/IN1_A: J5.4, R13.1, U2.3 (IN1)
/IN1_B: J6.1, R23.1, U4.3 (IN1)
/IN2_A: J5.5, R14.1, U2.2 (IN2)
/IN2_B: J6.2, R24.1, U4.2 (IN2)
/LED_DIN: LED2.4 (DIN), R42.2
/LED_IO: J5.6, R41.2, R42.1
/OUT1_A: J2.1, U2.6 (OUT1)
/OUT1_B: J3.1, U4.6 (OUT1)
/OUT2_A: J2.2, U2.8 (OUT2)
/OUT2_B: J3.2, U4.8 (OUT2)
/QG: Q1.1 (G), R1.2, R2.1
/RS485_A: D3.1 (A1), J4.1, J4.4, JP2.2 (B), R33.1, U5.6 (A)
/RS485_B: D3.2 (A2), J4.2, J4.5, JP1.2, JP3.1 (A), U5.7 (B)
/RS_DE: J6.6, R32.1, U5.2 (~RE), U5.3 (DE)
/RS_DI: J6.8, U5.4 (DI)
/RS_RO: J6.7, R31.2, U5.1 (RO)
/SCL: J6.5, J7.3, R44.2, U1.5 (SCL), U3.5 (SCL)
/SDA: J6.4, J7.2, R43.2, U1.6 (SDA), U3.6 (SDA)
/TERM: JP1.1, R33.2
/VBAT: C1.1, C2.1, D1.1 (A1), PS1.1 (IN), Q1.2 (S), R1.1, R11.1, R21.1, U1.1 (IN+), U3.1 (IN+)
/VIN_F: F1.2, Q1.3 (D)
/VLED: C42.1, D4.1 (K), LED2.1 (VDD)
/VM_A: C12.1, C13.1, R11.2, U1.2 (IN-), U2.5 (VM)
/VM_B: C22.1, C23.1, R21.2, U3.2 (IN-), U4.5 (VM)

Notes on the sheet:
jaskier_door_lock variant C: two 12 V linear-actuator door locks on a socketed ESP32-C3 SuperMini, with an optional RS485 (Modbus RTU) port. Docs: hardware/door-lock-c/README.md
Supply: 4S LiFePO4 house bank, 10-14.6 V. F1 1.1 A PTC, Q1 P-MOSFET reverse-polarity switch (R1/R2 hold Vgs at -Vin/2, inside the AO3401A's 12 V limit), D1 16 V TVS: the INA219 bus input is 26 V max. PS1 5 V module (SIP-3, 7805 pinout). D2 feeds the SuperMini's 5V pin, so its USB-C and the 12 V sup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
Each door: VBAT -> 0.1 R shunt -> DRV8871 VM. The INA219 reads motor current and the bank voltage. Door A INA219 0x40 (A1 = A0 = GND), door B 0x44 (A1 = VS). Full on/off drive only, never PWM. R_ILIM 56k: DRV8871 current limit 64 kV / 56k = 1.14 A, above the 0.55 A stall measured in the van. 4.7k p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
Door contact input: reed or micro switch to GND (closed = door shut). 1k + 100n filter, 10k pull-up. Unconnected input reads high (open door). Swap M+/M- at the terminal if the bolt moves the wrong way.
ESP32-C3 SuperMini socket (antenna at the board edge): IO4/IO3 door A IN1/IN2, IO5/IO6 door B IN1/IN2, IO1 door A contact, IO0 door B contact, IO8/IO9 I2C SDA/SCL (pulled up: both strapping pins stay high at boot), IO2 status LED (strapping pin, 10k pull-up), IO10 RS485 DE/RE (10k pull-down), IO20 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
RS485, optional: Modbus RTU slave for control without Wi-Fi. DE/RE low at boot (R32), so the ROM boot log on IO21 never reaches the bus. JP1 120 ohm termination: fit a jumper cap on the last device of the bus. J4 has two A/B/GND sets for a pass-through. JP2/JP3 680 ohm fail-safe bias (bridge only i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

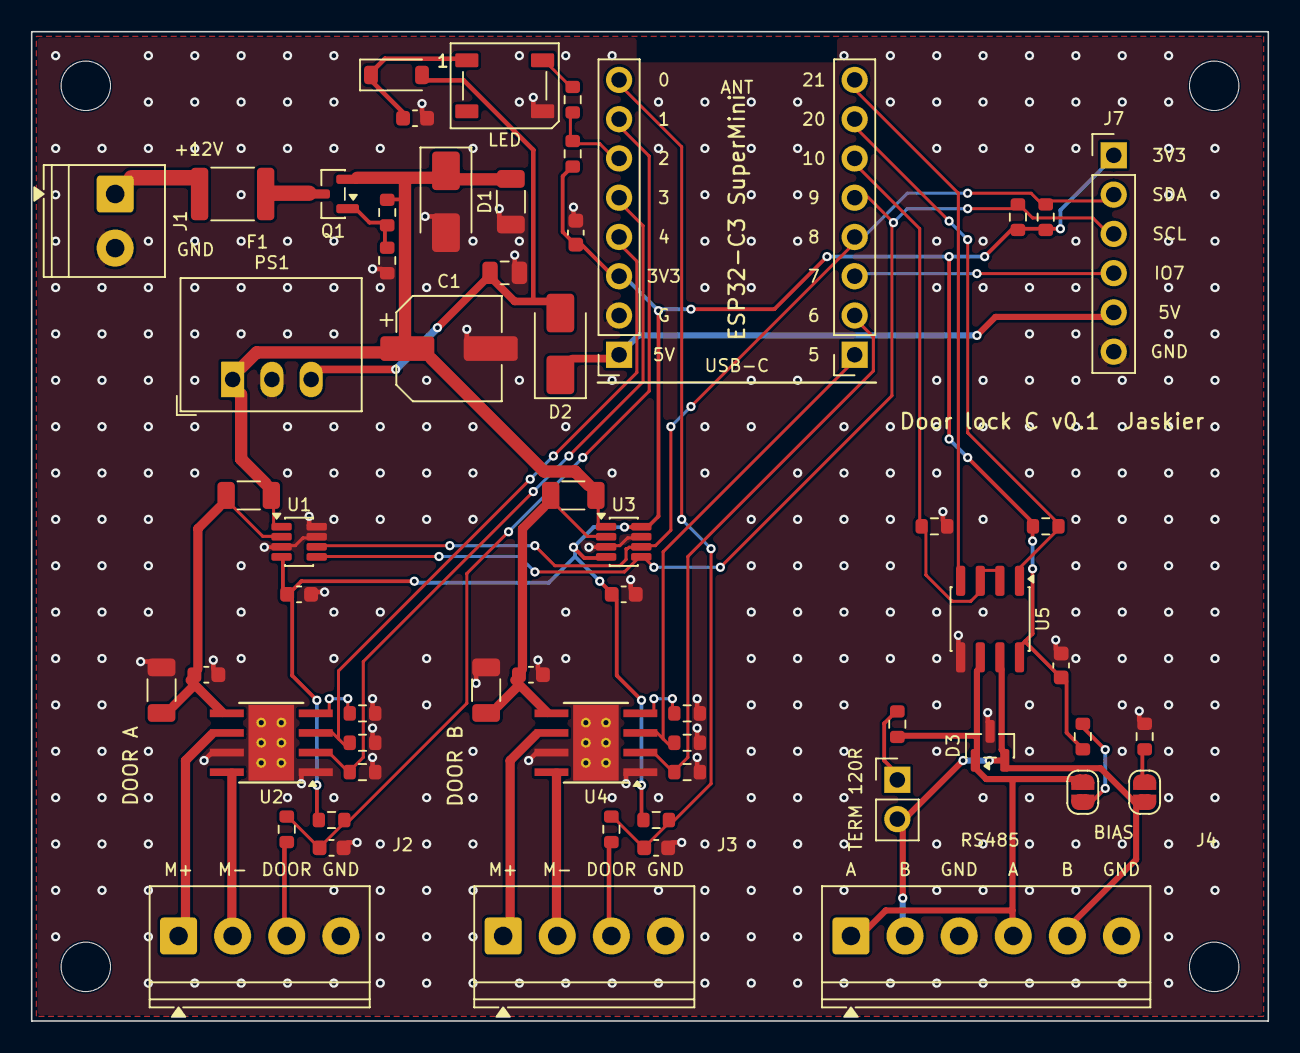
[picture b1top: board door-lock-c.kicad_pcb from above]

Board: 2 copper layers, 80.0 x 64.0 mm, 64 parts (0 on the bottom side), 38 nets.

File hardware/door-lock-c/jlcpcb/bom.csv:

Comment,Designator,Footprint,LCSC Part #
100u 35V,C1,CP_Elec_6.3x7.7,C72478
100n,"C11,C13,C14,C21,C23,C24,C31,C41,C42",C_0603_1608Metric,C14663
10u 50V,"C12,C2,C22",C_1206_3216Metric,C13585
10u 25V,C3,C_0805_2012Metric,C15850
SMAJ16A,D1,D_SMA,C364288
SS34,D2,D_SMA,C8678
SM712,D3,SOT-23,C172881
1N4148W,D4,D_SOD-123,C81598
1.1A 24V,F1,Fuse_1812_4532Metric,C883149
Power: +12V GND,J1,"TerminalBlock_Phoenix_PT-1,5-2-3.5-H_1x02_P3.50mm_Horizontal",C466970
Door A: M+ M- DOOR GND,J2,"TerminalBlock_Phoenix_PT-1,5-4-3.5-H_1x04_P3.50mm_Horizontal",C2757925
Door B: M+ M- DOOR GND,J3,"TerminalBlock_Phoenix_PT-1,5-4-3.5-H_1x04_P3.50mm_Horizontal",C2757925
RS485: A B GND A B GND,J4,"TerminalBlock_Phoenix_PT-1,5-6-3.5-H_1x06_P3.50mm_Horizontal",C5290323
"1x8 female 2.54 mm, 8.5 mm","J5,J6",PinSocket_1x08_P2.54mm_Vertical,C27438
Extension,J7,PinHeader_1x06_P2.54mm_Vertical,C492405
TERM 120R jumper,JP1,PinHeader_1x02_P2.54mm_Vertical,C492401
XL-5050RGBC-2812B,LED2,LED_WS2812B_PLCC4_5.0x5.0mm_P3.2mm,C2843785
K7805-500R3,PS1,Converter_DCDC_RECOM_R-78E-0.5_THT,C2992390
AO3401A,Q1,SOT-23,C15127
100k,"R1,R2",R_0603_1608Metric,C25803
0.1,"R11,R21",R_1206_3216Metric,C25334
56k,"R12,R22",R_0603_1608Metric,C23206
4.7k,"R13,R14,R23,R24,R43,R44",R_0603_1608Metric,C23162
1k,"R15,R25",R_0603_1608Metric,C21190
10k,"R16,R26,R31,R32,R41",R_0603_1608Metric,C25804
120,R33,R_0603_1608Metric,C22787
680,"R34,R35",R_0603_1608Metric,C23228
100,R42,R_0603_1608Metric,C22775
INA219AIDCNR,"U1,U3",SOT-23-8,C87469
DRV8871DDAR,"U2,U4",Texas_HTSOP-8-1EP_3.9x4.9mm_P1.27mm_EP2.95x4.9mm_Mask2.4x3.1mm_ThermalVias,C75864
SP3485EN,U5,SOIC-8_3.9x4.9mm_P1.27mm,C8963
